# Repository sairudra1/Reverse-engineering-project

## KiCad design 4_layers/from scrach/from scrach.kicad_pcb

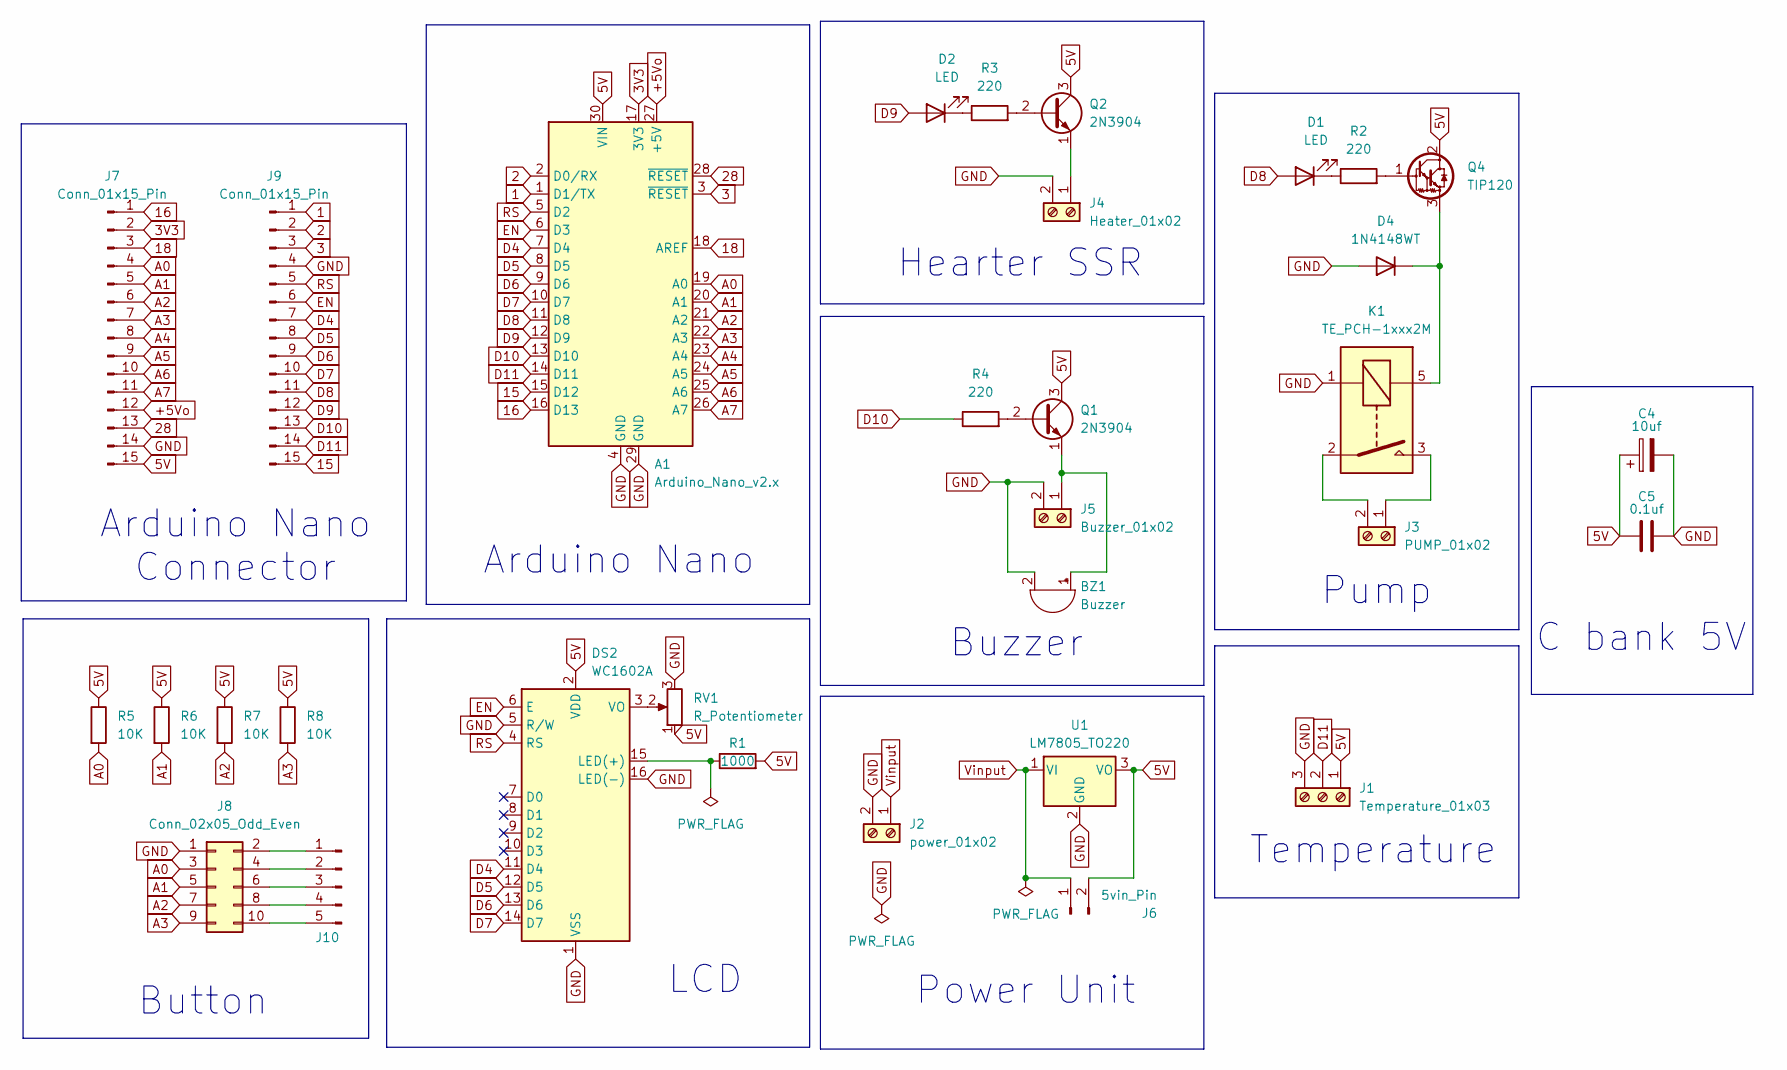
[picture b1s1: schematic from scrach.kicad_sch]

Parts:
A1: Arduino_Nano_v2.x; Arduino_Nano_WithMountingHoles
BZ1: Buzzer; Buzzer_12x9.5RM7.6
C4: 10uf; CP_Radial_D10.0mm_P5.00mm
C5: 0.1uf; C_Disc_D4.3mm_W1.9mm_P5.00mm
D1, D2: LED; LED_D3.0mm_Clear
D4: 1N4148WT; D_A-405_P10.16mm_Horizontal
DS2: WC1602A
J1: Temperature_01x03; TerminalBlock_Phoenix_MKDS-1,5-3-5.08_1x03_P5.08mm_Horizont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
J2: power_01x02; TerminalBlock_CUI_TB007-508-02_1x02_P5.08mm_Horizontal
J3: PUMP_01x02; TerminalBlock_CUI_TB007-508-02_1x02_P5.08mm_Horizontal
J4: Heater_01x02; TerminalBlock_CUI_TB007-508-02_1x02_P5.08mm_Horizontal
J5: Buzzer_01x02; TerminalBlock_CUI_TB007-508-02_1x02_P5.08mm_Horizontal
J6: 5vin_Pin; PinHeader_1x02_P2.54mm_Vertical
J7, J9: Conn_01x15_Pin; PinHeader_1x15_P2.54mm_Vertical
J8: Conn_02x05_Odd_Even; PinHeader_2x05_P2.54mm_Vertical
J10: Button_01x05_Pin; PinHeader_1x05_P2.54mm_Vertical
K1: TE_PCH-1xxx2M; Relay_SPST_TE_PCH-1xxx2M
Q1, Q2: 2N3904; TO-92_Inline
Q4: TIP120; TO-220-3_Vertical
R1: 1000; R_Axial_DIN0411_L9.9mm_D3.6mm_P15.24mm_Horizontal
R2, R3, R4: 220; R_Axial_DIN0411_L9.9mm_D3.6mm_P15.24mm_Horizontal
R5, R6, R7, R8: 10K; R_Axial_DIN0411_L9.9mm_D3.6mm_P15.24mm_Horizontal
RV1: R_Potentiometer; Potentiometer_Bourns_3386P_Vertical
U1: LM7805_TO220; TO-220-3_Vertical

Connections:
1: A1.1 (D1/TX), J9.1
2: A1.2 (D0/RX), J9.2
3: A1.3 (~RESET), J9.3
3V3: A1.17 (3V3), J7.2
5V: A1.30 (VIN), C4.1, C5.1, DS2.2 (VDD), J1.1, J6.2, J7.15, Q1.3 (C), Q2.3 (C), Q4.2 (C), R1.2, R5.1, R6.1, R7.1, R8.1, RV1.1, U1.3 (VO)
15: A1.15 (D12), J9.15
16: A1.16 (D13), J7.1
18: A1.18 (AREF), J7.3
28: A1.28 (~RESET), J7.13
+5Vo: A1.27 (+5V), J7.12
A0: A1.19 (A0), J7.4, J8.3, R5.2
A1: A1.20 (A1), J7.5, J8.5, R6.2
A2: A1.21 (A2), J7.6, J8.7, R7.2
A3: A1.22 (A3), J7.7, J8.9, R8.2
A4: A1.23 (A4), J7.8
A5: A1.24 (A5), J7.9
A6: A1.25 (A6), J7.10
A7: A1.26 (A7), J7.11
D4: A1.7 (D4), DS2.11 (D4), J9.7
D5: A1.8 (D5), DS2.12 (D5), J9.8
D6: A1.9 (D6), DS2.13 (D6), J9.9
D7: A1.10 (D7), DS2.14 (D7), J9.10
D8: A1.11 (D8), D1.2 (A), J9.11
D9: A1.12 (D9), D2.2 (A), J9.12
D10: A1.13 (D10), J9.13, R4.1
D11: A1.14 (D11), J1.2, J9.14
EN: A1.6 (D3), DS2.6 (E), J9.6
GND: A1.4 (GND), A1.29 (GND), BZ1.2 (-), C4.2, C5.2, D4.2 (A), DS2.1 (VSS), DS2.5 (R/W), DS2.16 (LED(-)), J1.3, J2.2, J4.2, J5.2, J7.14, J8.1, J9.4, K1.1, RV1.3, U1.2 (GND)
unnamed: BZ1.1 (+), J5.1, Q1.1 (E)
unnamed: D1.1 (K), R2.1
unnamed: D2.1 (K), R3.1
unnamed: D4.1 (K), K1.5, Q4.3 (E)
unnamed: DS2.15 (LED(+)), R1.1
unnamed: DS2.3 (VO), RV1.2
unnamed: J3.1, K1.3
unnamed: J3.2, K1.2
unnamed: J4.1, Q2.1 (E)
unnamed: J8.2, J10.1
unnamed: J8.4, J10.2
unnamed: J8.6, J10.3
unnamed: J8.8, J10.4
unnamed: J8.10, J10.5
unnamed: Q1.2 (B), R4.2
unnamed: Q2.2 (B), R3.2
unnamed: Q4.1 (B), R2.2
RS: A1.5 (D2), DS2.4 (RS), J9.5
Vinput: J2.1, J6.1, U1.1 (VI)

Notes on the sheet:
Arduino Nano
Button
Pump
C bank 5V
LCD
Buzzer
Temperature
Arduino Nano Connector
Hearter SSR
Power Unit

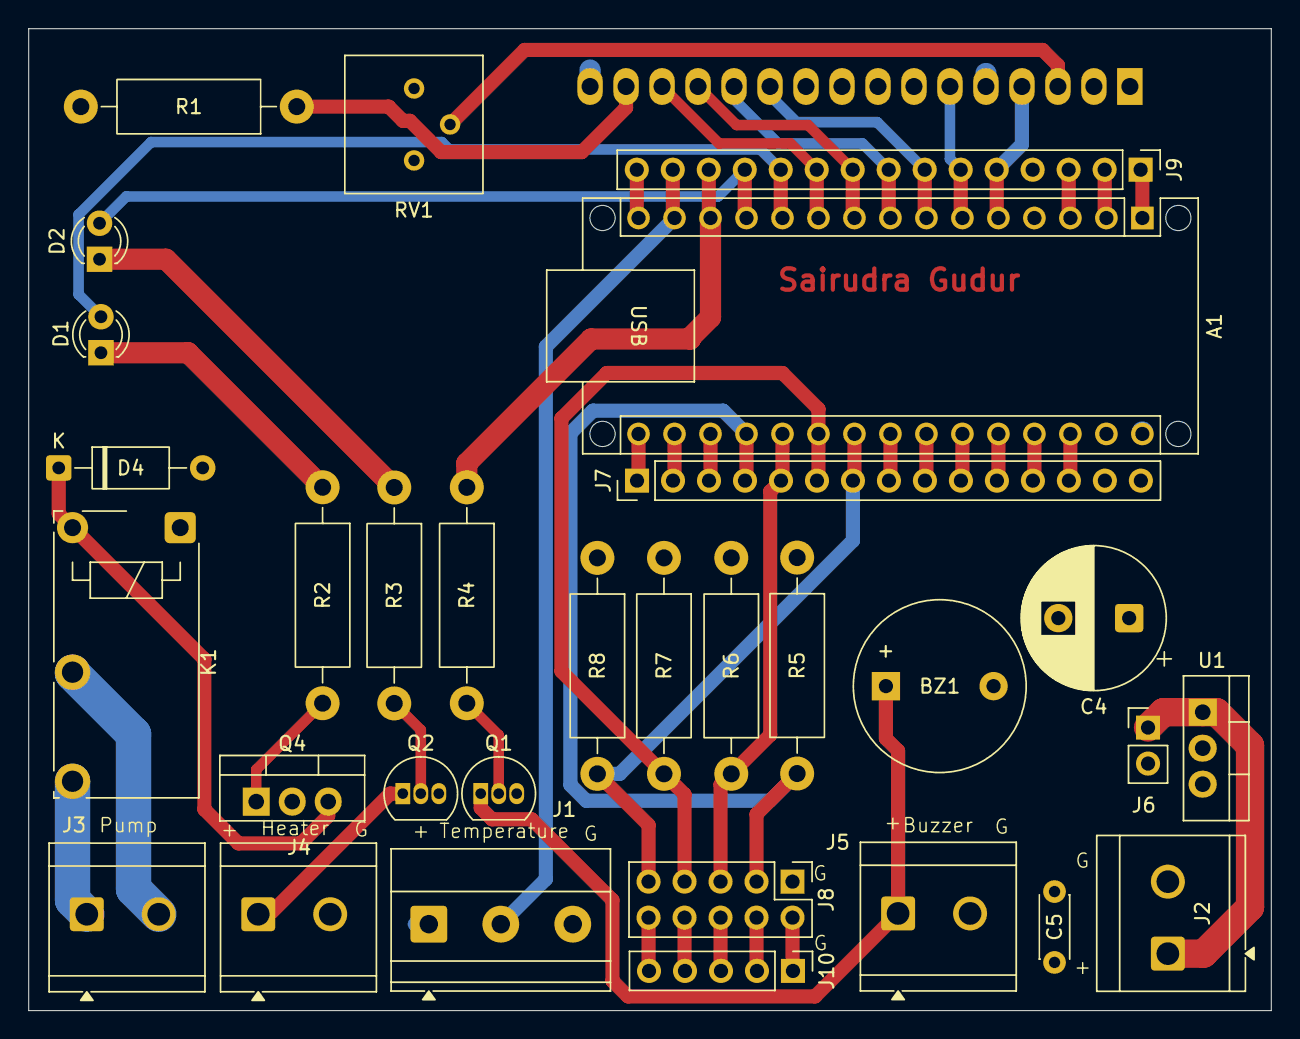
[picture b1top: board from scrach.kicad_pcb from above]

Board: 4 copper layers, 87.7 x 69.3 mm, 32 parts (1 on the bottom side), 47 nets.

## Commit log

2025-11-29 commit 1
2025-11-29 extra redundant
2026-01-19 4 kayer design
